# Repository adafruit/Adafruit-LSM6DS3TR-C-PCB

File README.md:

## Adafruit LSM6DS3TR-C 6-DoF Accel + Gyro IMU - STEMMA QT / Qwiic PCB

<a href="http://www.adafruit.com/products/4503"><br/>
Click here to purchase one from the Adafruit shop</a>

PCB files for the Adafruit LSM6DS3TR-C 6-DoF Accel + Gyro IMU - STEMMA QT / Qwiic. 

Format is EagleCAD schematic and board layout
* https://www.adafruit.com/product/4503

### Description

Add motion and orientation sensing to your Arduino project with this affordable 6 Degree of Freedom (6-DoF) sensor with sensors from ST. The board includes an ST LSM6DS3TR-C, a great entry-level 6-DoF IMU accelerometer + gyro. The 3-axis accelerometer can tell you which direction is down towards the Earth (by measuring gravity) or how fast the board is accelerating in 3D space. The 3-axis gyroscope can measure spin and twist.

This chip is very similar to the now-discontinued LSM6DS33, a great entry-level IMU. As part of the illustrious LSM6DS family, its well-established, well-supported and this chip even has better performance! Note it is not firmware-compatible with the 'DS33, so you will need to recompile code (e.g our Arduino and Python libraries support the whole family but you do have to indicate which exact chip you're using)

To make getting started fast and easy, we placed the sensors on a compact breakout board with voltage regulation and level-shifted inputs. That way you can use them with 3V or 5V power/logic devices without worry. Both I2C and SPI interfaces are available, so you'll be able to use them with any hardware setup. The breakout comes fully assembled and tested, with some extra header so you can use it on a breadboard. Four mounting holes make for a secure connection.

This breakout does not include a magnetometer, often required for accurate orientation. We recommend the LIS3MDL 3-axis magnetometer to match up with this IMU.

Additionally, since it speaks I2C you can easily connect it up with two wires (plus power and ground!).  We've even included SparkFun qwiic compatible STEMMA QT connectors for the I2C bus so you don't even need to solder! Just wire up to your favorite micro like the STM32F405 Feather with a plug-and-play cable to get 6 DoF data ASAP. You can change the I2C address on the back using the solder jumper, to have two of these sensor boards on one bus.

We also wrote libraries to help you get these sensors integrated with your Arduino/C++. This library contains an Arduino driver for the accel/gyro. For advanced Arduino usage, ST has their own fully-featured library that includes extras such as FIFO management and tap detection for the LSM6DS3TR-C. We also have a Python/CircuitPython library that will work on microcontroller or single board linux computers.

### License

Adafruit invests time and resources providing this open source design, please support Adafruit and open-source hardware by purchasing products from [Adafruit](https://www.adafruit.com)!

Designed by Limor Fried/Ladyada for Adafruit Industries.

Creative Commons Attribution/Share-Alike, all text above must be included in any redistribution. 
See license.txt for additional details.

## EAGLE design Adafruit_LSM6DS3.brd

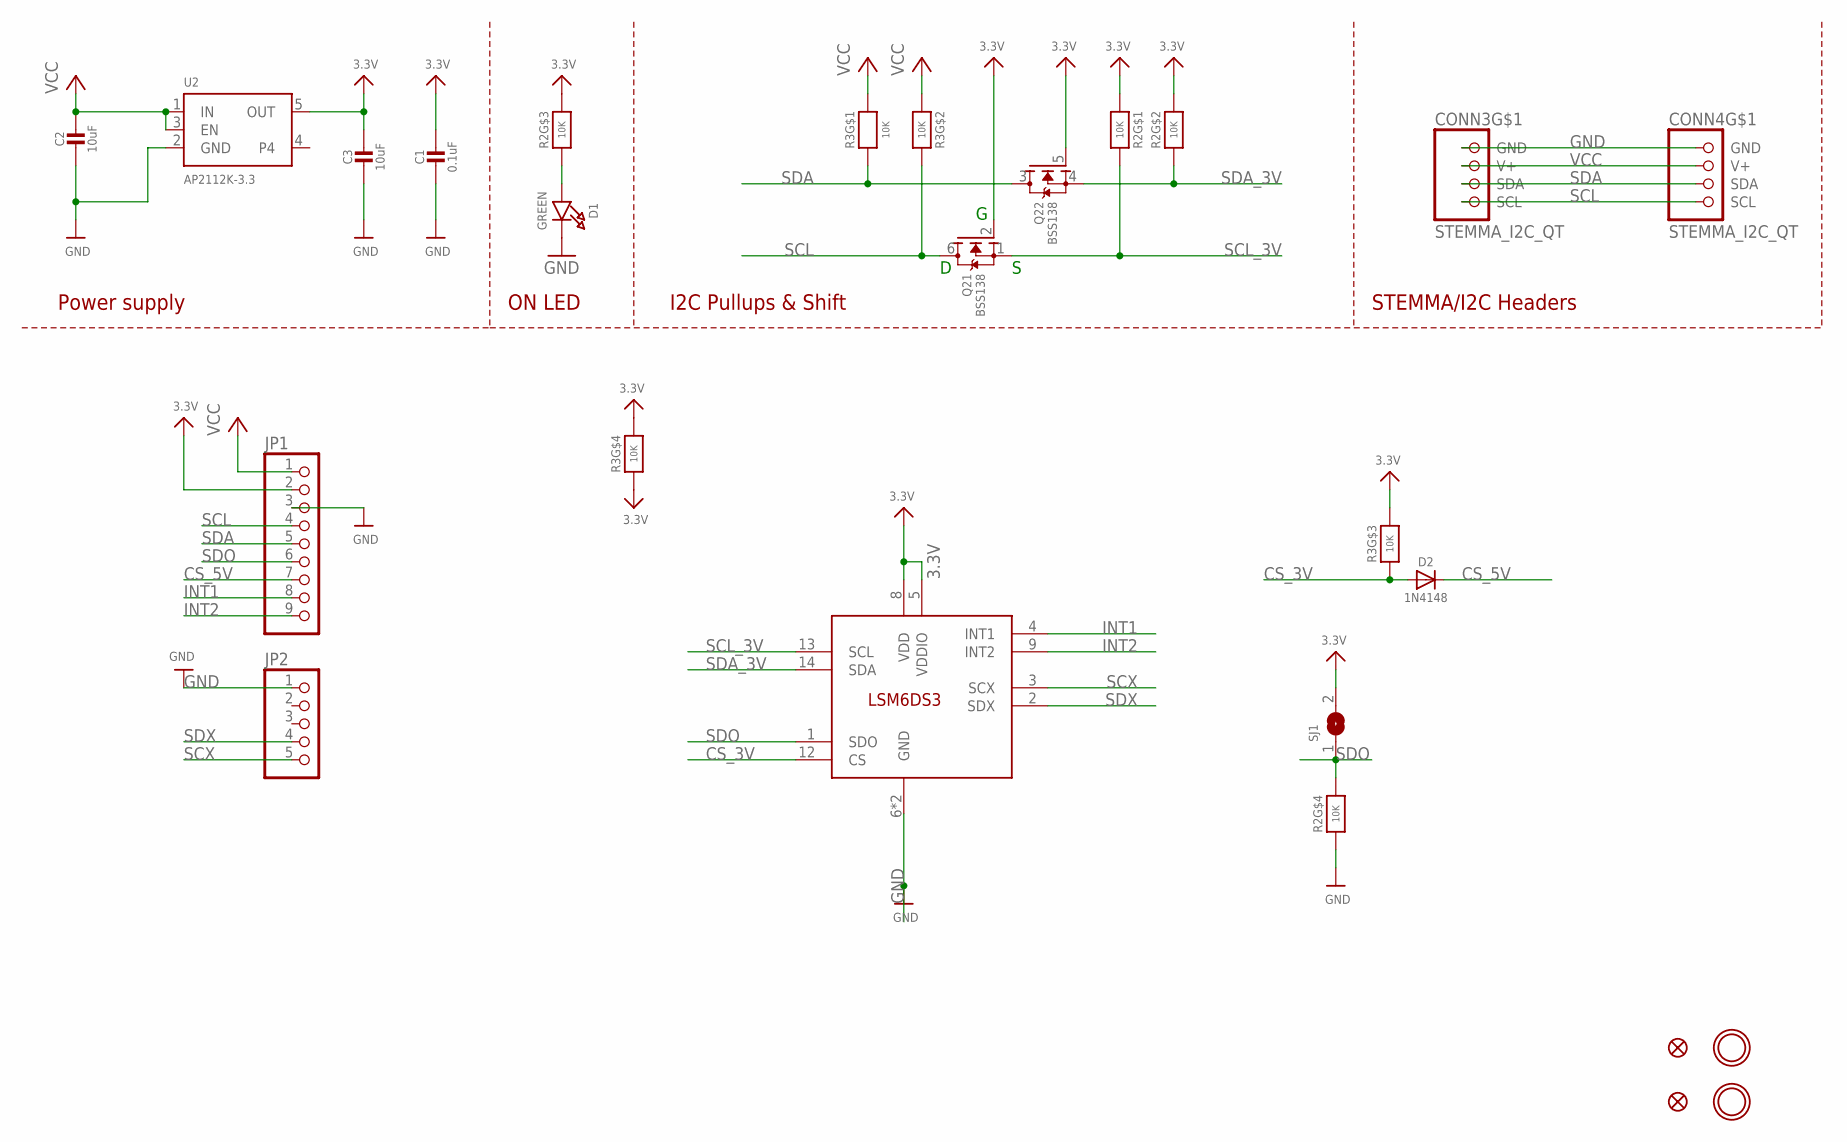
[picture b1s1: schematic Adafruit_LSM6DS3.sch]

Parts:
C1: 0.1uF; 0603-NO
C2, C3: 10uF; 0805-NO
CONN3, CONN4: STEMMA_I2C_QT; JST_SH4
D1: GREEN; CHIPLED_0603_NOOUTLINE
D2: 1N4148; SOD-323
FID3, FID4: FIDUCIAL_1MM
JP1: HEADER-1X970MIL; 1X09_ROUND_70
JP2: HEADER-1X570MIL; 1X05_ROUND_70
Q2: BSS138; SOT363
R2, R3: 10K; RESPACK_4X0603
SJ1: SOLDERJUMPER; SOLDERJUMPER_ARROW_NOPASTE
U1: LSM6DS3; LGA-14L
U2: AP2112K-3.3; SOT23-5
U$1, U$17: MOUNTINGHOLE2.5; MOUNTINGHOLE_2.5_PLATED

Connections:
3.3V: C1.1, C3.1, JP1.2, Q2.2 (G), Q2.5 (G), R2.1, R2.2 (1), R2.6 (2), R3.3 (1), R3.4 (1), R3.5 (2), SJ1.2, U1.5 (VDDIO), U1.8 (VDD), U2.5 (OUT)
CS_3V: D2.A, R3.6 (2), U1.12 (CS)
CS_5V: D2.C, JP1.7
GND: C1.2, C2.2, C3.2, CONN3.1 (GND), CONN4.1 (GND), D1.C, JP1.3, JP2.1, R2.4 (1), U1.6 (GND), U1.7 (GND), U2.2 (GND)
INT1: JP1.8, U1.4 (INT1)
INT2: JP1.9, U1.9 (INT2)
unnamed: D1.A, R2.3 (1)
SCL: CONN3.4 (SCL), CONN4.4 (SCL), JP1.4, Q2.6 (D), R3.2 (1)
SCL_3V: Q2.1 (S), R2.8 (2), U1.13 (SCL)
SCX: JP2.5, U1.3 (SCX)
SDA: CONN3.3 (SDA), CONN4.3 (SDA), JP1.5, Q2.3 (D), R3.1
SDA_3V: Q2.4 (S), R2.7 (2), U1.14 (SDA)
SDO: JP1.6, R2.5 (2), SJ1.1, U1.1 (SDO)
SDX: JP2.4, U1.2 (SDX)
VCC: C2.1, CONN3.2 (V+), CONN4.2 (V+), JP1.1, R3.7 (2), R3.8 (2), U2.1 (IN), U2.3 (EN)

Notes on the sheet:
I2C Pullups & Shift
STEMMA/I2C Headers
ON LED
Power supply

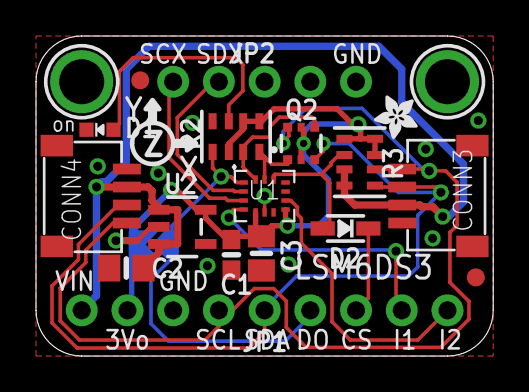
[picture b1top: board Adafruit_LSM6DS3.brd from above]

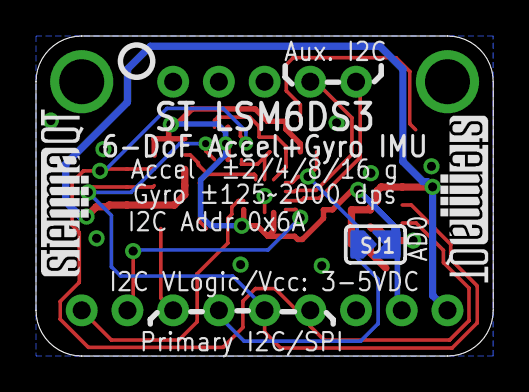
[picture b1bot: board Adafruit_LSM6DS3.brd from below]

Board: 2 copper layers, 25.4 x 17.8 mm, 23 parts (4 on the bottom side), 15 nets.

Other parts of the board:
U$9: ADAFRUIT_2.5MM
U$25: PCBFEAT-REV-040
U$30, U$31: STEMMAQT

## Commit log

2022-07-11 adding cookiecutter
2022-07-11 updating image

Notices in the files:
parts and their libraries:
microbuilder: This work is placed in the public domain, and may be freely used for commercial and non-commercial work with the following conditions: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
